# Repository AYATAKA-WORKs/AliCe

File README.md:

# AliCe
This is my micromouse project in 2017 version.

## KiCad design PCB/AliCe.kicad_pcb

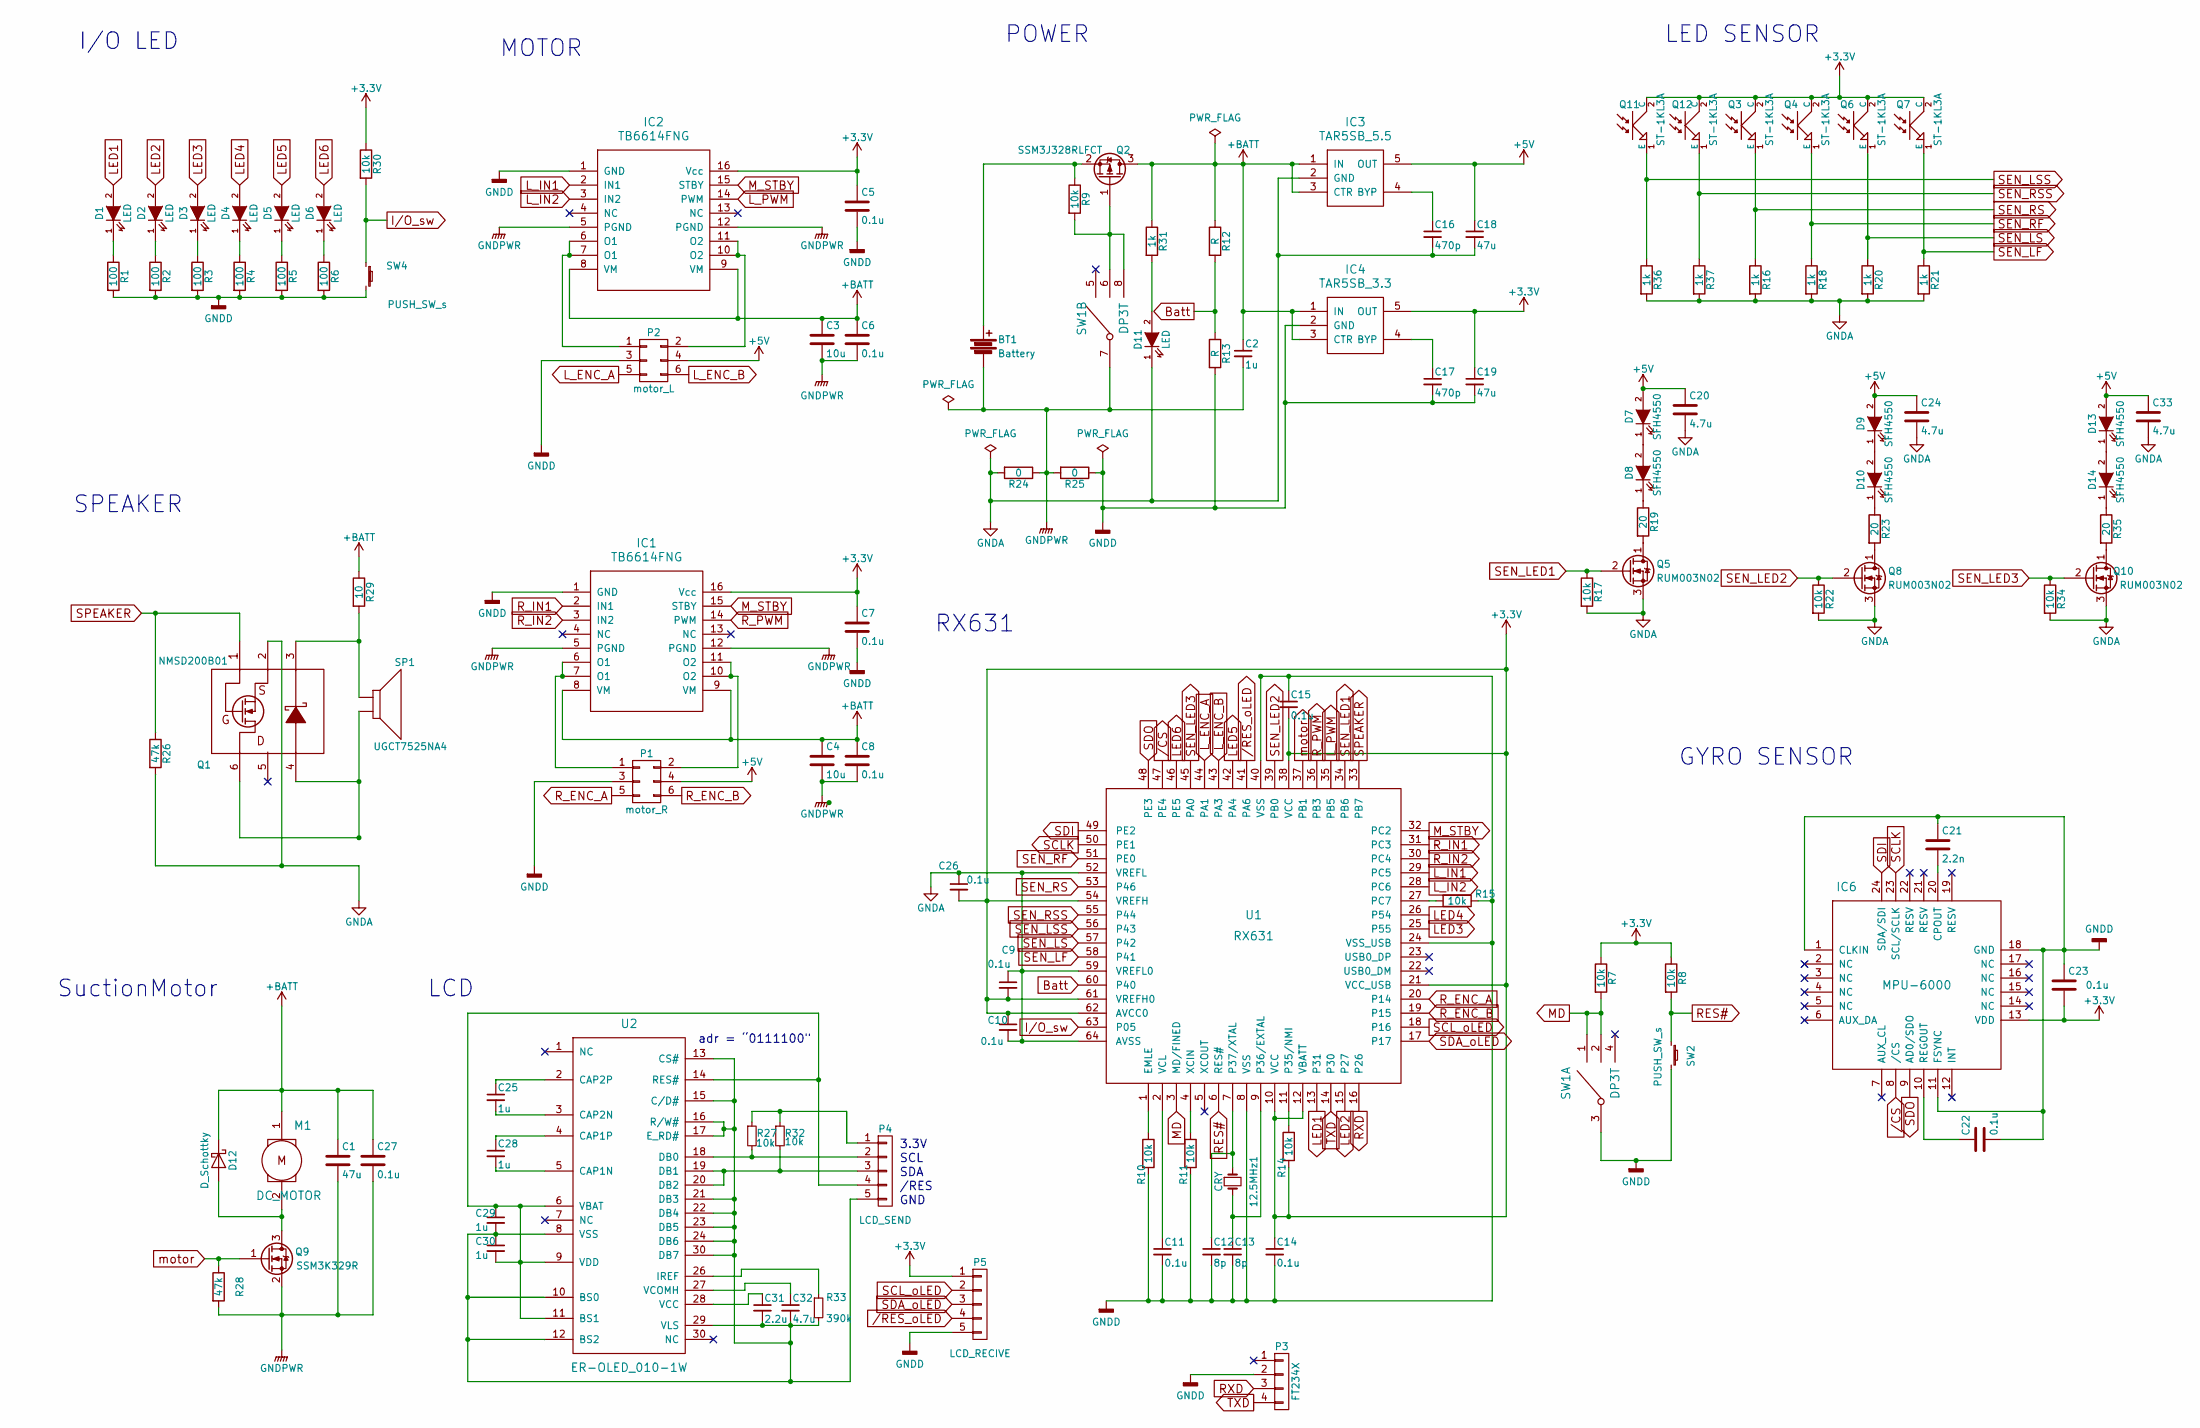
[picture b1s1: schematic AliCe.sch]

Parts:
12.5MHz1: CRY; CRY_4-SMD
BT1: Battery; pin_con_2mm
C1, C18, C19: 47u; C_0603
C2, C25, C28, C29, C30: 1u; C_0603
C3, C4: 10u; C_0603
C5, C6, C7, C8, C9, C10, C11, C14, C15, C22, C23, C26, C27: 0.1u; C_0603
C12, C13: 8p; C_0603
C16, C17: 470p; C_0603
C20, C24, C32, C33: 4.7u; C_0603
C21: 2.2n; C_0603
C31: 2.2u; C_0603
D1, D2, D3, D4, D5, D6, D11: LED; LED_0603
D7, D8, D9, D10, D13, D14: SFH4550; LED_D3.0mm
D12: D_Schottky; SOD-128
IC1, IC2: TB6614FNG; SSOP-16_4.4x5.2mm_Pitch0.65mm
IC3: TAR5SB_5.5; SSOP5-P-0.95
IC4: TAR5SB_3.3; SSOP5-P-0.95
IC6: MPU-6000; QFN-24-1EP_4x4mm_Pitch0.5mm
M1: DC_MOTOR; Pin_Header_Straight_1x02_Pitch2.54mm
P1: motor_R; Pin_Header_Straight_2x03_Pitch2.00mm
P2: motor_L; Pin_Header_Straight_2x03_Pitch2.00mm
P3: FT234X; Pin_Header_Straight_1x04_Pitch2.54mm
P4: LCD_SEND; FFC_connect_pitch1.0x5
P5: LCD_RECIVE; FFC_connect_pitch1.0x5
Q1: NMSD200B01; SOT-363
Q2: SSM3J328RLFCT; SOT-23
Q3, Q4, Q6, Q7, Q11, Q12: ST-1KL3A; Pin_Header_Straight_1x02_Pitch2.54mm
Q5, Q8, Q10: RUM003N02; SOT-723
Q9: SSM3K329R; SOT-23
R1, R2, R3, R4, R5, R6: 100; R_0402_NoSilk
R7, R8, R9, R10, R11, R14, R15, R17, R22, R27, R30, R32, R34: 10k; R_0402_NoSilk
R12, R13: R; R_0402_NoSilk
R16, R18, R20, R21, R31, R36, R37: 1k; R_0402_NoSilk
R19, R23, R35: 20; R_0402_NoSilk
R24: 0; R_0402_NoSilk
R25: 0; check_2pin_1.6mm
R26, R28: 47k; R_0402_NoSilk
R29: 10; R_0402_NoSilk
R33: 390k; R_0402_NoSilk
SP1: UGCT7525NA4; UGCT7525AN4
SW1: DP3T; JS203011AQN
SW2, SW4: PUSH_SW_s; PTS810
U1: RX631; LQFP-64_10x10mm_Pitch0.5mm
U2: ER-OLED_010-1W; ER-OLED010-1

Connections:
+3V3: C5.1, C7.1, C9.2, C10.1, C14.1, C15.2, C19.1, C23.2, C26.2, IC1.16 (Vcc), IC2.16 (Vcc), IC4.5 (OUT), IC6.13 (VDD), P5.1, Q3.2 (C), Q4.2 (C), Q6.2 (C), Q7.2 (C), Q11.2 (C), Q12.2 (C), R7.1, R8.1, R14.2, R30.1, U1.10 (VCC), U1.12 (VBATT), U1.21 (VCC_USB), U1.38 (VCC), U1.54 (VREFH), U1.61 (VREFH0), U1.62 (AVCC0)
+5V: C18.1, C20.1, C24.1, C33.1, D7.2 (A), D9.2 (A), D13.2 (A), IC3.5 (OUT), P1.4, P2.4
+BATT: C1.1, C2.1, C3.1, C4.1, C6.1, C8.1, C27.1, D12.1 (K), IC1.8 (VM), IC1.9 (VM), IC2.8 (VM), IC2.9 (VM), IC3.1 (IN), IC3.3 (CTR), IC4.1 (IN), IC4.3 (CTR), M1.1, Q2.3 (D), R12.1, R29.1, R31.1
/CS: IC6.8 (/CS), U1.47 (PE4)
/RES_oLED: P5.4, U1.41 (PA6)
Batt: R12.2, R13.1, U1.60 (P40)
GNDA: C9.1, C10.2, C16.2, C18.2, C20.2, C24.2, C26.1, C33.2, D11.1 (K), IC3.2 (GND), Q1.2 (S_Q1), Q5.3 (S), Q8.3 (S), Q10.3 (S), R16.2, R17.2, R18.2, R20.2, R21.2, R22.2, R24.2, R26.2, R34.2, R36.2, R37.2, U1.52 (VREFL), U1.59 (VREFL0), U1.64 (AVSS)
GNDD: C5.2, C7.2, C11.2, C12.2, C13.2, C14.2, C15.1, C17.2, C19.2, C21.1, C22.2, C23.1, IC1.1 (GND), IC2.1 (GND), IC4.2 (GND), IC6.1 (CLKIN), IC6.11 (FSYNC), IC6.18 (GND), P1.3, P2.3, P3.2, P5.5, R1.2, R2.2, R3.2, R4.2, R5.2, R6.2, R10.2, R11.2, R13.2, R15.1, R25.1, SW1.3, SW2.2, SW4.2, U1.8 (VSS), U1.24 (VSS_USB), U1.40 (VSS)
GNDPWR: BT1.2, C1.2, C2.2, C3.2, C4.2, C6.2, C8.2, C27.2, IC1.5 (PGND), IC1.12 (PGND), IC2.5 (PGND), IC2.12 (PGND), Q9.2 (S), R24.1, R25.2, R28.2, SW1.7
I/O_sw: R30.2, SW4.1, U1.63 (P05)
LED1: D1.2 (A), U1.13 (P31)
LED2: D2.2 (A), U1.15 (P27)
LED3: D3.2 (A), U1.25 (P55)
LED4: D4.2 (A), U1.26 (P54)
LED5: D5.2 (A), U1.42 (PA4)
LED6: D6.2 (A), U1.46 (PE5)
L_ENC_A: P2.5, U1.44 (PA1)
L_ENC_B: P2.6, U1.43 (PA3)
L_IN1: IC2.2 (IN1), U1.29 (PC5)
L_IN2: IC2.3 (IN2), U1.28 (PC6)
L_PWM: IC2.14 (PWM), U1.35 (PB5)
MD: R7.2, SW1.1, SW1.2, U1.3 (MD/FINED)
M_STBY: IC1.15 (STBY), IC2.15 (STBY), U1.32 (PC2)
unnamed: 12.5MHz1.1, C12.1, U1.7 (P37/XTAL)
unnamed: 12.5MHz1.2, C13.1, U1.9 (P36/EXTAL)
unnamed: BT1.1, Q2.2 (S), R9.1
unnamed: C11.1, U1.2 (VCL)
unnamed: C16.1, IC3.4 (BYP)
unnamed: C17.1, IC4.4 (BYP)
unnamed: C21.2, IC6.20 (CPOUT)
unnamed: C22.1, IC6.10 (REGOUT)
unnamed: C25.1, U2.2 (CAP2P)
unnamed: C25.2, U2.3 (CAP2N)
unnamed: C28.1, U2.4 (CAP1P)
unnamed: C28.2, U2.5 (CAP1N)
unnamed: C29.1, C30.2, P4.4, U2.6 (VBAT), U2.9 (VDD), U2.11 (BS1), U2.14 (RES#)
unnamed: C29.2, C30.1, C31.2, C32.2, P4.5, R33.2, U2.8 (VSS), U2.10 (BS0), U2.12 (BS2), U2.13 (CS#), U2.15 (C/D#), U2.16 (R/W#), U2.17 (E_RD#), U2.21 (DB3), U2.22 (DB4), U2.23 (DB5), U2.24 (DB6), U2.29 (VLS), U2.30 (DB7)
unnamed: C31.1, U2.28 (VCC)
unnamed: C32.1, U2.27 (VCOMH)
unnamed: D1.1 (K), R1.1
unnamed: D2.1 (K), R2.1
unnamed: D3.1 (K), R3.1
unnamed: D4.1 (K), R4.1
unnamed: D5.1 (K), R5.1
unnamed: D6.1 (K), R6.1
unnamed: D7.1 (K), D8.2 (A)
unnamed: D8.1 (K), R19.1
unnamed: D10.1 (K), R23.1
unnamed: D9.1 (K), D10.2 (A)
unnamed: D11.2 (A), R31.2
unnamed: D12.2 (A), M1.2, Q9.3 (D)
unnamed: D13.1 (K), D14.2 (A)
unnamed: D14.1 (K), R35.1
unnamed: IC1.6 (O1), IC1.7 (O1), P1.1
unnamed: IC1.10 (O2), IC1.11 (O2), P1.2
unnamed: IC2.6 (O1), IC2.7 (O1), P2.1
unnamed: IC2.10 (O2), IC2.11 (O2), P2.2
unnamed: P4.1, R27.1, R32.1
unnamed: P4.2, R27.2, U2.18 (DB0)
unnamed: P4.3, R32.2, U2.19 (DB1), U2.20 (DB2)
unnamed: Q1.3 (C_D1), R29.2, SP1.1
unnamed: Q1.4 (A_D1), Q1.6 (D_Q1), SP1.2
unnamed: Q2.1 (G), R9.2, SW1.6, SW1.8
unnamed: Q5.1 (D), R19.2
unnamed: Q8.1 (D), R23.2
unnamed: Q10.1 (D), R35.2
unnamed: R10.1, U1.1 (EMLE)
unnamed: R11.1, U1.4 (XCIN)
unnamed: R14.1, U1.11 (P35/NMI)
unnamed: R15.2, U1.27 (PC7)
unnamed: R33.1, U2.26 (IREF)
RES#: R8.2, SW2.1, U1.6 (RES#)
RXD: P3.3, U1.16 (P26)
R_ENC_A: P1.5, U1.20 (P14)
R_ENC_B: P1.6, U1.19 (P15)
R_IN1: IC1.2 (IN1), U1.31 (PC3)
R_IN2: IC1.3 (IN2), U1.30 (PC4)
R_PWM: IC1.14 (PWM), U1.36 (PB3)
SCLK: IC6.23 (SCL/SCLK), U1.50 (PE1)
SCL_oLED: P5.2, U1.18 (P16)
SDA_oLED: P5.3, U1.17
SDI: IC6.24 (SDA/SDI), U1.49 (PE2)
SDO: IC6.9 (AD0/SDO), U1.48 (PE3)
SEN_LED1: Q5.2 (G), R17.1, U1.34 (PB6)
SEN_LED2: Q8.2 (G), R22.1, U1.39 (PB0)
SEN_LED3: Q10.2 (G), R34.1, U1.45 (PA0)
SEN_LF: Q7.1 (E), R21.1, U1.58 (P41)
SEN_LS: Q6.1 (E), R20.1, U1.57 (P42)
SEN_LSS: Q11.1 (E), R36.1, U1.56 (P43)
SEN_RF: Q4.1 (E), R18.1, U1.51 (PE0)
SEN_RS: Q3.1 (E), R16.1, U1.53 (P46)
SEN_RSS: Q12.1 (E), R37.1, U1.55 (P44)
SPEAKER: Q1.1 (G_Q1), R26.1, U1.33 (PB7)
TXD: P3.4, U1.14 (P30)
motor: Q9.1 (G), R28.1, U1.37 (PB1)

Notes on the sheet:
LED SENSOR
GYRO SENSOR
RX631
MOTOR
POWER
I/O LED
SPEAKER
SuctionMotor
LCD
adr = “0111100"
3.3V
SCL
SDA
/RES
GND

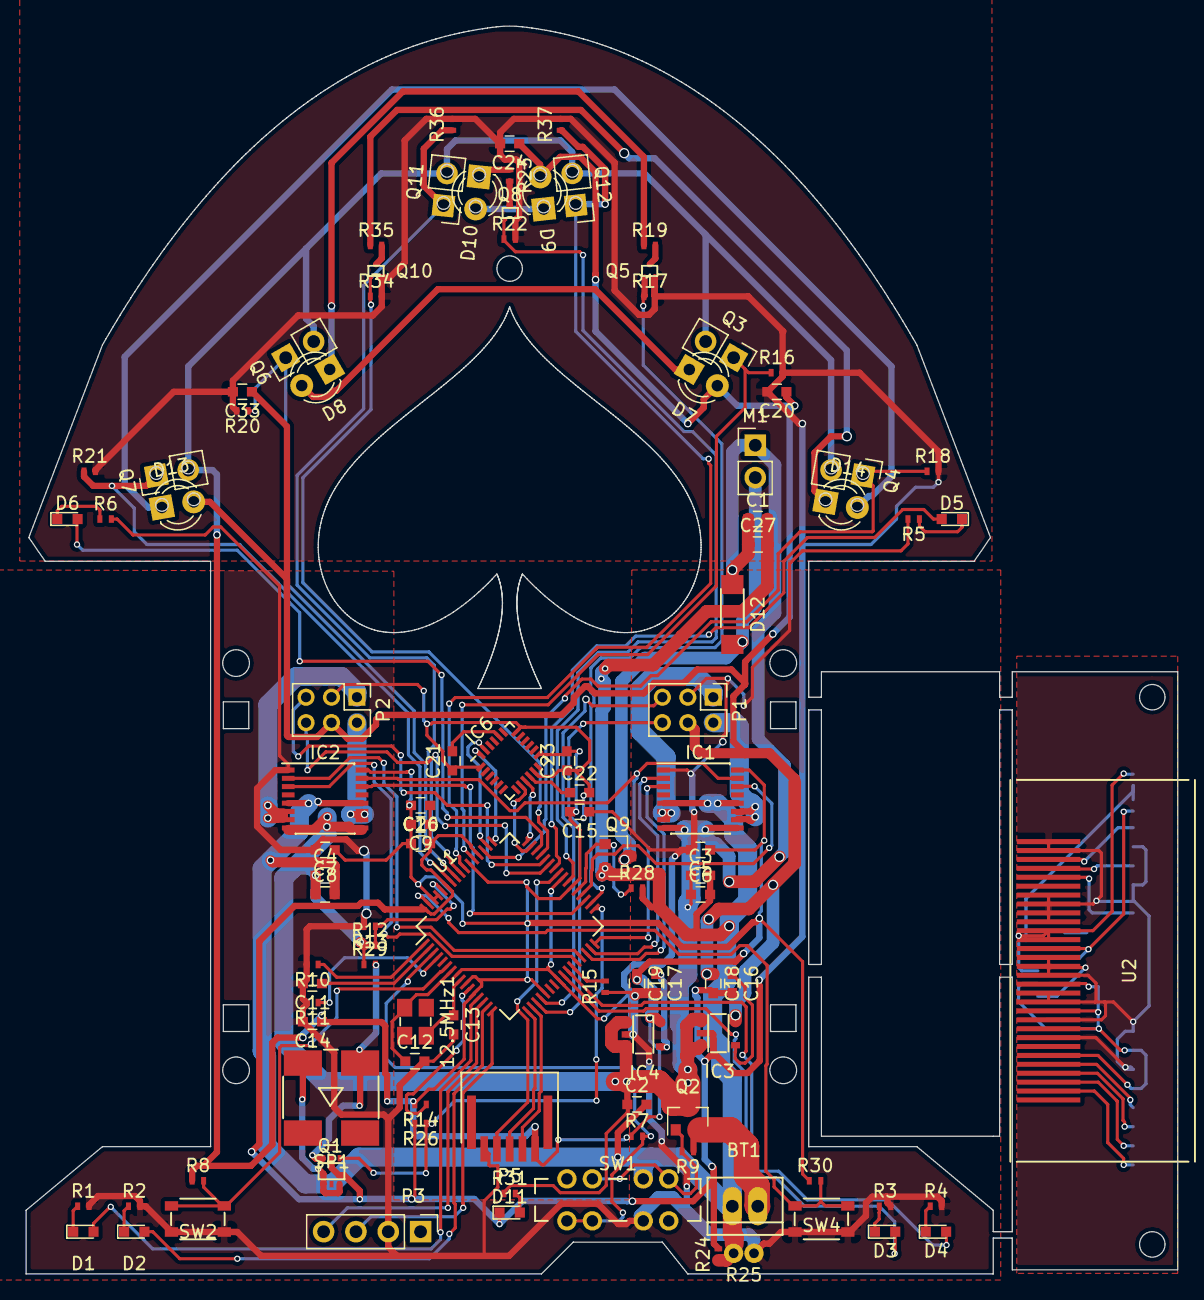
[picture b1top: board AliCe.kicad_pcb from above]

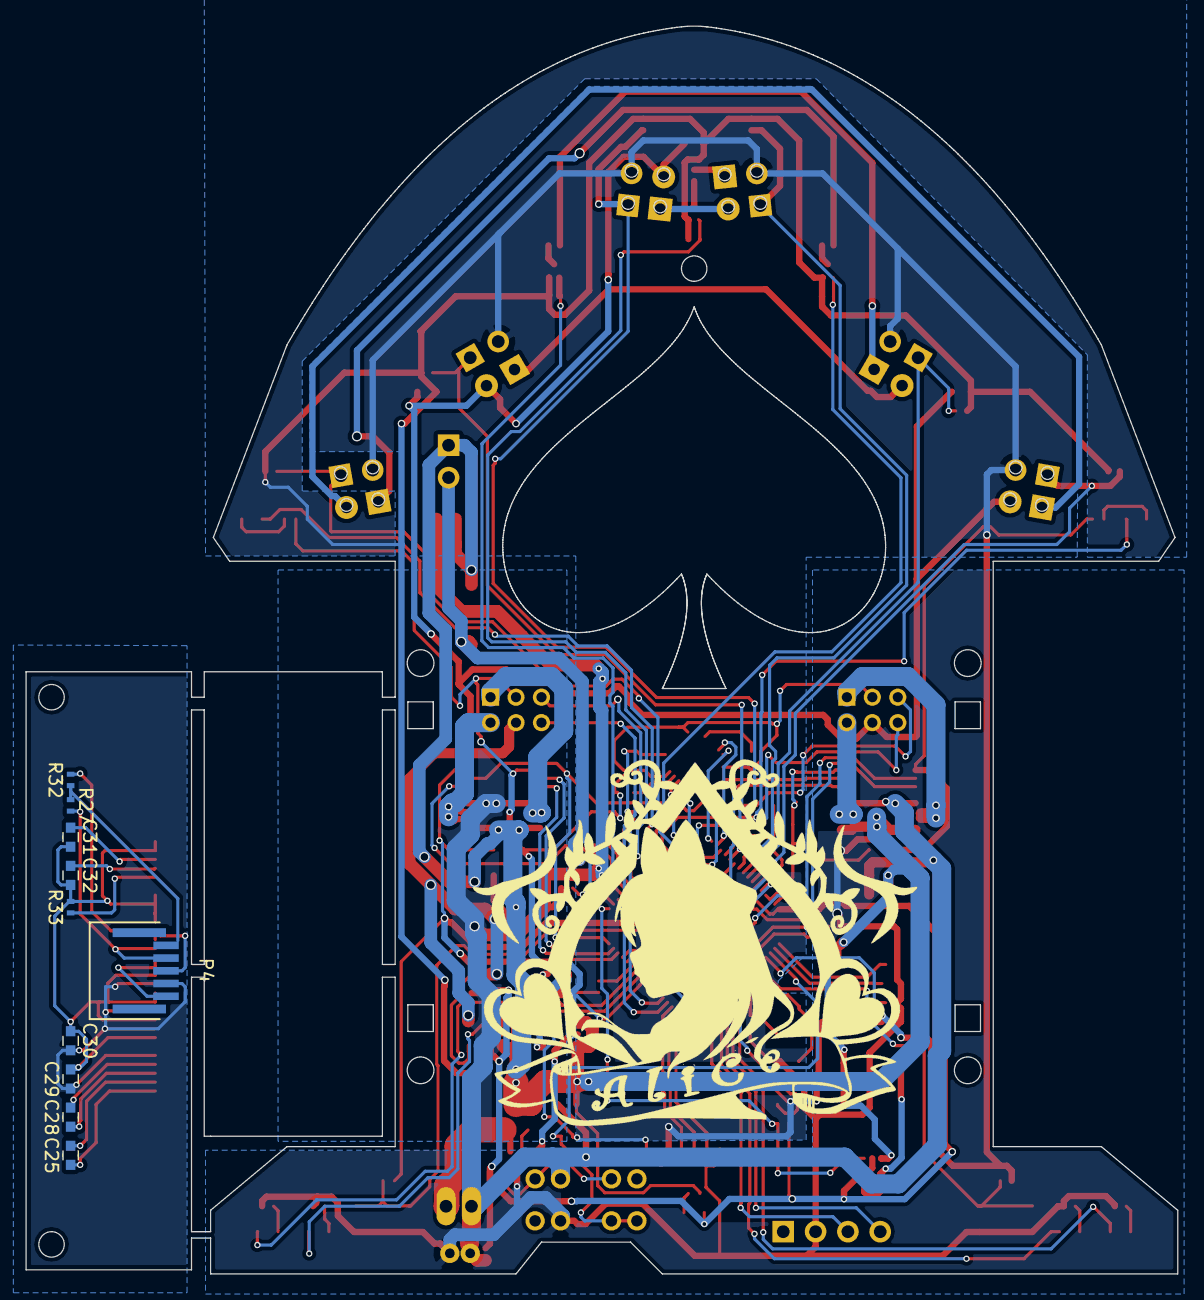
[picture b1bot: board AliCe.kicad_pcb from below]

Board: 2 copper layers, 90.5 x 98.1 mm, 115 parts (10 on the bottom side), 95 nets.

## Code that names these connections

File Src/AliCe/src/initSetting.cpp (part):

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	//---------------------------------------------------------------
	//モータ用(MTU4,TPU4)の設定
	//---------------------------------------------------------------
	PORTB.PMR.BIT.B3 = 0x1u;    //PB3:周辺機器を使用 R_PWM
	PORTB.PMR.BIT.B5 = 0x1u;    //PB5:周辺機器を使用 L_PWM

	MPC.PWPR.BYTE = 0x00;       //PSWEレジスタへの書き込み禁止

	MPC.PWPR.BYTE = 0x40u;      //PFSレジスタへの書き込み許可
	MPC.PB3PFS.BIT.PSEL = 0x2u; //PB3をMTIOC4Aに設定
	MPC.PB5PFS.BIT.PSEL = 0x3u; //PB5をTIOCB4に設定
	MPC.PWPR.BYTE = 0x80u;      //PFSレジスタをプロテクト

	SYSTEM.PRCR.WORD = 0xa50b;  //プロテクトされたレジスタを全て解除
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	//---------------------------------------------------------------
	//スピーカー用(TPU5)の設定
	//---------------------------------------------------------------
	PORTB.PMR.BIT.B7 = 0x1u;    //PB7:周辺機器を使用

	MPC.PWPR.BYTE = 0x00;       //PSWEレジスタへの書き込み禁止
	MPC.PWPR.BYTE = 0x40u;      //PFSレジスタへの書き込み許可
	MPC.PB7PFS.BIT.PSEL = 0x3u; //PB7をMTIOC0Aに設定
	MPC.PWPR.BYTE = 0x80u;      //PFSレジスタをプロテクト

	PORTB.PDR.BIT.B7 = 0x1u;    //PB7：出力

	SYSTEM.PRCR.WORD = 0xa50b;  //プロテクトされたレジスタを全て解除
	MSTP(TPU5) = 0;             //モジュールストップ機能 0:解除,1:停止
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	//---------------------------------------------------------------
	//吸引モーター(MTU0)の設定
	//---------------------------------------------------------------
	PORTB.PMR.BIT.B1 = 0x1u;    //PB1:周辺機器を使用 MTIOC0C

	MPC.PWPR.BYTE = 0x00;       //PSWEレジスタへの書き込み禁止

	MPC.PWPR.BYTE = 0x40u;      //PFSレジスタへの書き込み許可
	MPC.PB1PFS.BIT.PSEL = 0x1u; //PB3をMTIOC3Cに設定
	MPC.PWPR.BYTE = 0x80u;      //PFSレジスタをプロテクト

	SYSTEM.PRCR.WORD = 0xa50b;  //プロテクトされたレジスタを全て解除
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//I/Oの設定
//-------------------------------------------------------------------
void initSetting::initIO(void) {
	PORT3.PDR.BIT.B1 = 1;	//LED1
	PORT2.PDR.BIT.B7 = 1;	//LED2
	PORT5.PDR.BIT.B5 = 1;	//LED3
	PORT5.PDR.BIT.B4 = 1;	//LED4
	PORTA.PDR.BIT.B4 = 1;	//LED5
	PORTE.PDR.BIT.B5 = 1;	//LED6

	PORTB.PDR.BIT.B6 = 1;	// SEN_LED1(Middle)
	PORTB.PDR.BIT.B0 = 1;	// SEN_LED2(Side)
	PORTA.PDR.BIT.B0 = 1;	// SEN_LED3(Front)

	PORT0.PCR.BIT.B5 = 1;	// P05:入力プルアップ

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	//I/Oピンの設定
	MPC.PWPR.BYTE = 0x00;         //PSWEレジスタへの書き込み禁止
	MPC.PWPR.BYTE = 0x40u;        //PFSレジスタへの書き込み許可
	MPC.PE1PFS.BIT.PSEL = 0x0E;   //PE1をRSPCKBに設定
	MPC.PE2PFS.BIT.PSEL = 0x0E;   //PE2をMOSIBに設定
	MPC.PE3PFS.BIT.PSEL = 0x0D;   //PE3をMISOBに設定
	MPC.PE4PFS.BIT.PSEL = 0x0D;   //PE4をSSLB0に設定
	MPC.PWPR.BYTE = 0x80u;        //PFSレジスタをプロテクト

	PORTE.PMR.BIT.B1 = 1;         //PE1を周辺機能として設定
	PORTE.PMR.BIT.B2 = 1;         //PE2を周辺機能として設定
	PORTE.PMR.BIT.B3 = 1;         //PE3を周辺機能として設定
	PORTE.PMR.BIT.B4 = 1;         //PE4を周辺機能として設定

	RSPI1.SPCR.BYTE = 0;          //SPI機能停止
	RSPI1.SPSR.BYTE = 0xa0;       //ステータスレジスタクリア
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	MSTP(MTU2) = 0;                 //
	SYSTEM.PRCR.WORD = 0xA500;      //レジスタをプロテクト

	PORTA.PMR.BIT.B1 = 1;           //PA1を周辺機能として設定
	PORTA.PMR.BIT.B3 = 1;           //PA3を周辺機能として設定

	MTU2.TMDR.BIT.MD = 4;           //位相計数モード1に設定
	MTU2.TCNT = 32767;              //TCNT初期値

	MPC.PWPR.BIT.B0WI = 0;          //プロテクト解除
	MPC.PWPR.BIT.PFSWE = 1;
	MPC.PA1PFS.BIT.PSEL = 0x02;     //PA1をMTCLKCに設定
	MPC.PA3PFS.BIT.PSEL = 0x02;     //PA3をMTCLKDに設定
	MPC.PWPR.BIT.PFSWE = 0;         //プロテクト
	MPC.PWPR.BIT.B0WI = 1;
}
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
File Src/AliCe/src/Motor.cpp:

#include "Motor.h"
#include "iodefine.h"
#include "initSetting.h"
#include "parameter.h"

Motor::Motor(char _LorR){
	LorR = _LorR;
}
void Motor::setParameter(char _LorR){
	if(_LorR == L){
		LorR = L;
	}
	else {
		LorR = R;
	}
}

void Motor::cw(void){
	M_STBY = 1;
	if(LorR == L){
		L_IN1 = 0;
		L_IN2 = 1;;	// L_PWM
	}
	else{
		R_IN1 = 1;
		R_IN2 = 0;	// R_PWM
	}
}

void Motor::ccw(void){
	M_STBY = 1;
	if(LorR == L){
		L_IN1 = 1;
		L_IN2 = 0;	// L_PWM
	}
	else{
		R_IN1 = 0;
		R_IN2 = 1;	// R_PWM
	}
}

void Motor::enable(void){
	M_STBY = 1;
	if(LorR == L){
		CSTR(TPU4) = 1;	// L_PWM
	}
	else{
		CSTR(MTU4) = 1;	// R_PWM
	}
}

void Motor::disable(void){
	M_STBY = 0;
	if(LorR == L){
		CSTR(TPU4) = 0;	// L_PWM
	}
	else{
		CSTR(MTU4) = 0;	// R_PWM
	}
}

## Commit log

2018-06-24 edit README
2018-06-24 edit PID
2018-09-11 edit param
2018-10-01 edit fixdis
2018-10-13 edit tier
2018-12-05 1.5m/sターンを追加&ターンの後ろ距離の壁制御を修正
